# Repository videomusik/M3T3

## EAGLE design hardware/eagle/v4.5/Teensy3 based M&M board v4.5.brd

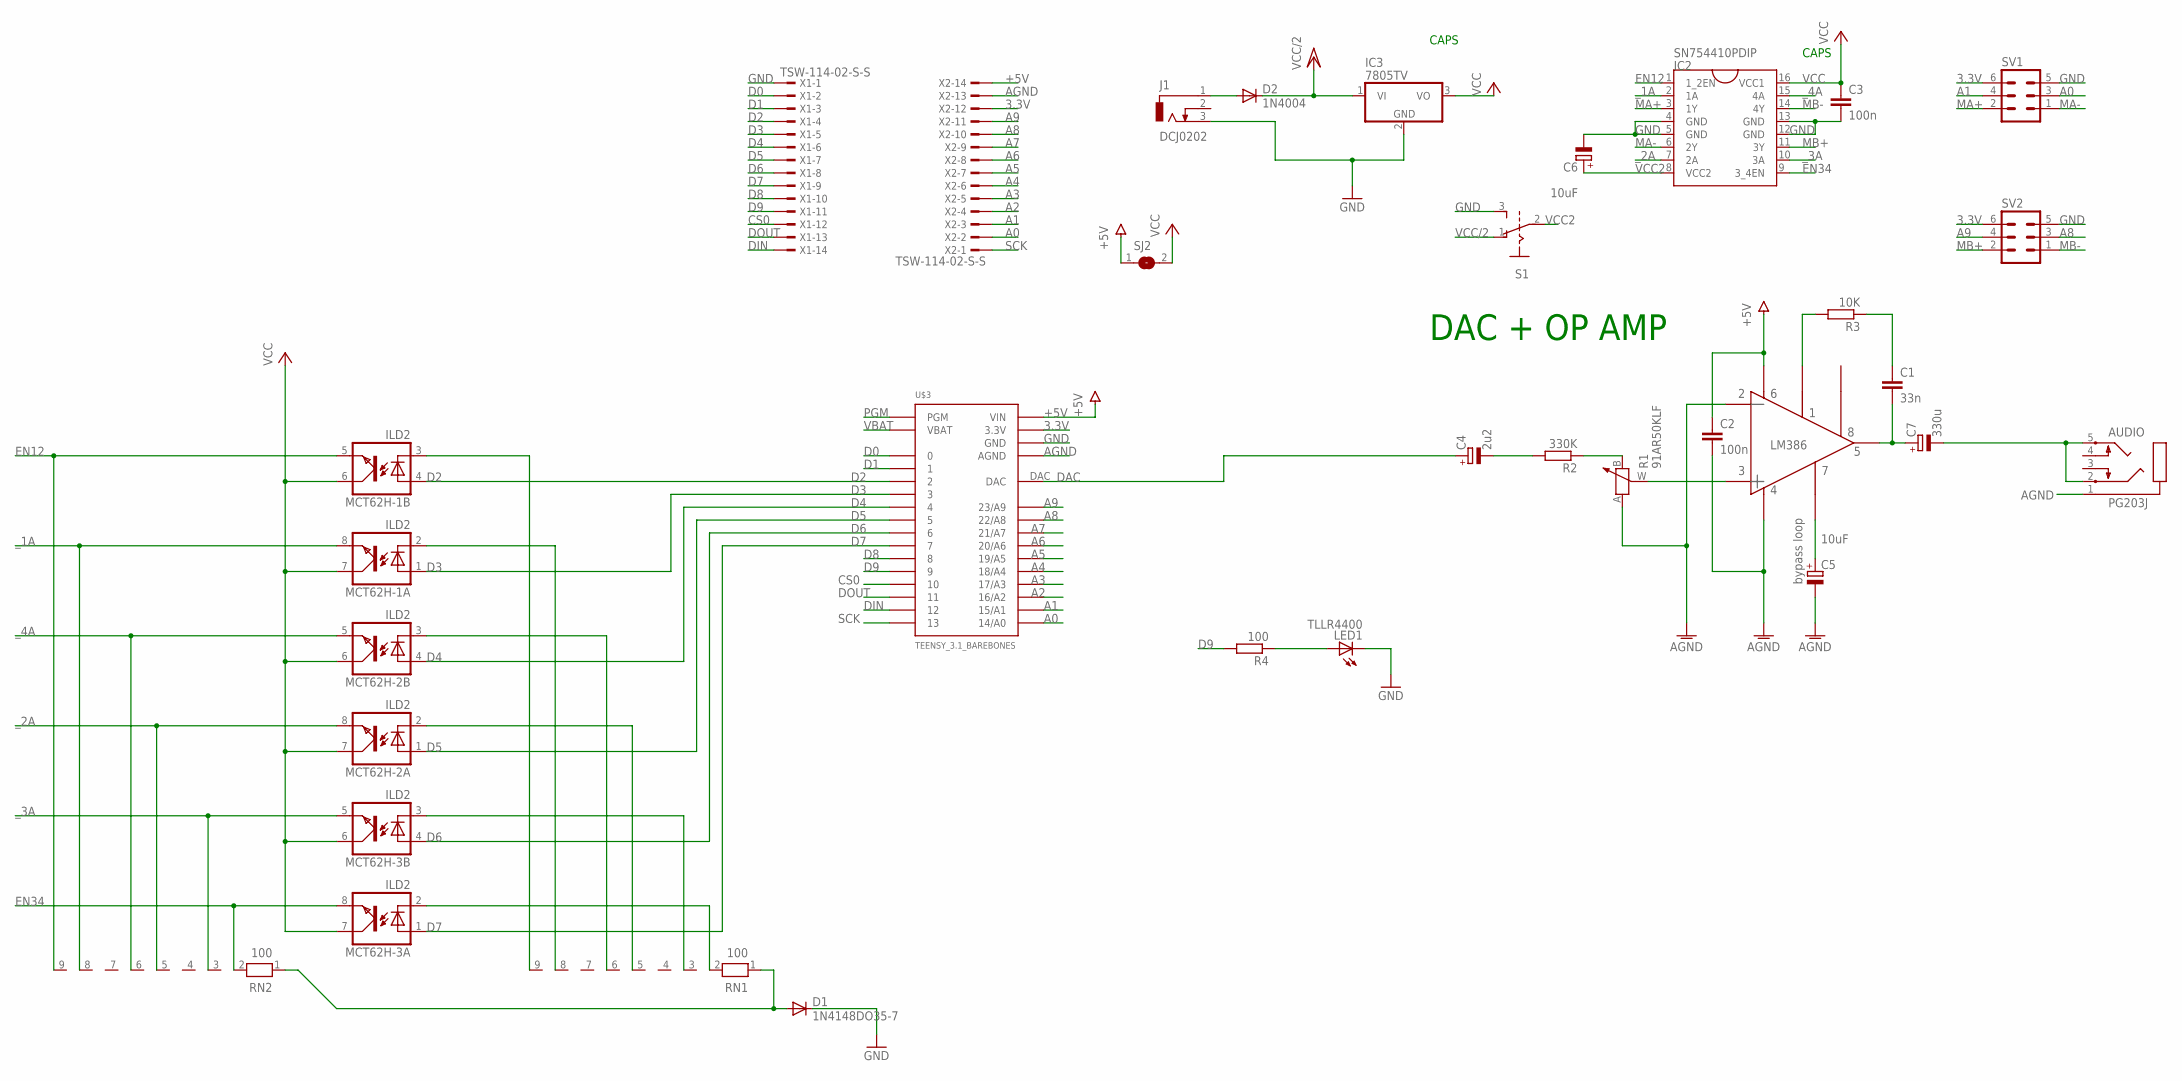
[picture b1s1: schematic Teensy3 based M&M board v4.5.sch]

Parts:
AUDIO: PG203J
C1: 33n; C050-030X075
C2, C3: 100n; C050-030X075
C4: 2u2; E2-5
C5, C6: 10uF; E2-5
C7: 330u; E2,5-7
D1: 1N4148DO35-7; DO35-7
D2: 1N4004; DO41-10
IC2: SN754410PDIP; DIL16
IC3: 7805TV; TO220V
J1: DCJ0202
LED1: TLLR4400; LED3MM
MCT62H-1, MCT62H-2, MCT62H-3: ILD2; DIL08
R1: 91AR50KLF
R2: 330K; 0207/7
R3: 10K; 0207/7
R4: 100; 0207/7
RN1, RN2: 100; RN-9
S1: EG1218; GF-126-0159
SJ2: SJ
SV1, SV2: ML6
U$2: LM386
U$3: TEENSY_3.1_BAREBONES
X1, X2: TSW-114-02-S-S

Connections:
3.3V: SV1.6, SV2.6, U$3.3.3V1 (3.3V), U$3.3.3V2 (3.3V), X2.12
+5V: C2.1, SJ2.1, U$2.6, U$3.VIN, X2.14
A0: SV1.3, U$3.14/A0, X2.2
A1: SV1.4, U$3.15/A1, X2.3
A2: U$3.16/A2, X2.4
A3: U$3.17/A3, X2.5
A4: U$3.18/A4, X2.6
A5: U$3.19/A5, X2.7
A6: U$3.20/A6, X2.8
A7: U$3.21/A7, X2.9
A8: SV2.3, U$3.22/A8, X2.10
A9: SV2.4, U$3.23/A9, X2.11
AGND: AUDIO.1, C2.2, C5.-, R1.A, U$2.2, U$2.4, U$3.AGND, X2.13
AMP_IN: R1.W, U$2.3
CS0: U$3.10, X1.12
D0: U$3.0, X1.2
D1: U$3.1, X1.3
D2: MCT62H-1.4 (A), U$3.2, X1.4
D3: MCT62H-1.1 (A), U$3.3, X1.5
D4: MCT62H-2.4 (A), U$3.4, X1.6
D5: MCT62H-2.1 (A), U$3.5, X1.7
D6: MCT62H-3.4 (A), U$3.6, X1.8
D7: MCT62H-3.1 (A), U$3.7, X1.9
D8: U$3.8, X1.10
D9: R4.2, U$3.9, X1.11
DAC: C4.+, U$3.DAC
DIN: U$3.12, X1.14
DOUT: U$3.11, X1.13
EN12: IC2.1 (1_2EN), MCT62H-1.5 (EMIT), RN2.9
EN34: IC2.9 (3_4EN), MCT62H-3.8 (EMIT), RN2.2
GND: C3.2, C6.-, D1.C, IC2.4 (GND), IC2.5 (GND), IC2.12 (GND), IC2.13 (GND), IC3.2 (GND), J1.3, LED1.K (C), S1.3, SV1.5, SV2.5, U$3.GND1 (GND), U$3.GND2 (GND), X1.1
MA+: IC2.3 (1Y), SV1.2
MA-: IC2.6 (2Y), SV1.1
MB+: IC2.11 (3Y), SV2.2
MB-: IC2.14 (4Y), SV2.1
unnamed: D2.A, J1.1
unnamed: R3.2, U$2.1
unnamed: C4.-, R2.2
unnamed: LED1.A, R4.1
unnamed: R1.B, R2.1
unnamed: D1.A, RN1.1, RN2.1
unnamed: C1.1, R3.1
unnamed: C5.+, U$2.7
unnamed: MCT62H-3.2 (C), RN1.2
unnamed: MCT62H-1.3 (C), RN1.9
unnamed: MCT62H-1.2 (C), RN1.8
unnamed: MCT62H-2.3 (C), RN1.6
unnamed: MCT62H-2.2 (C), RN1.5
unnamed: MCT62H-3.3 (C), RN1.3
unnamed: AUDIO.2, AUDIO.5, C7.-
unnamed: C1.2, C7.+, U$2.5
PGM: U$3.PGM
SCK: U$3.13, X2.1
VBAT: U$3.VBAT
VCC: C3.1, IC2.16 (VCC1), IC3.3 (VO), MCT62H-1.6 (COL), MCT62H-1.7 (COL), MCT62H-2.6 (COL), MCT62H-2.7 (COL), MCT62H-3.6 (COL), MCT62H-3.7 (COL), SJ2.2
VCC2: C6.+, IC2.8 (VCC2), S1.2
VCC/2: D2.C, IC3.1 (VI), S1.1
_1A: IC2.2 (1A), MCT62H-1.8 (EMIT), RN2.8
_2A: IC2.7 (2A), MCT62H-2.8 (EMIT), RN2.5
_3A: IC2.10 (3A), MCT62H-3.5 (EMIT), RN2.3
_4A: IC2.15 (4A), MCT62H-2.5 (EMIT), RN2.6

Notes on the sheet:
DAC + OP AMP
bypass loop
CAPS

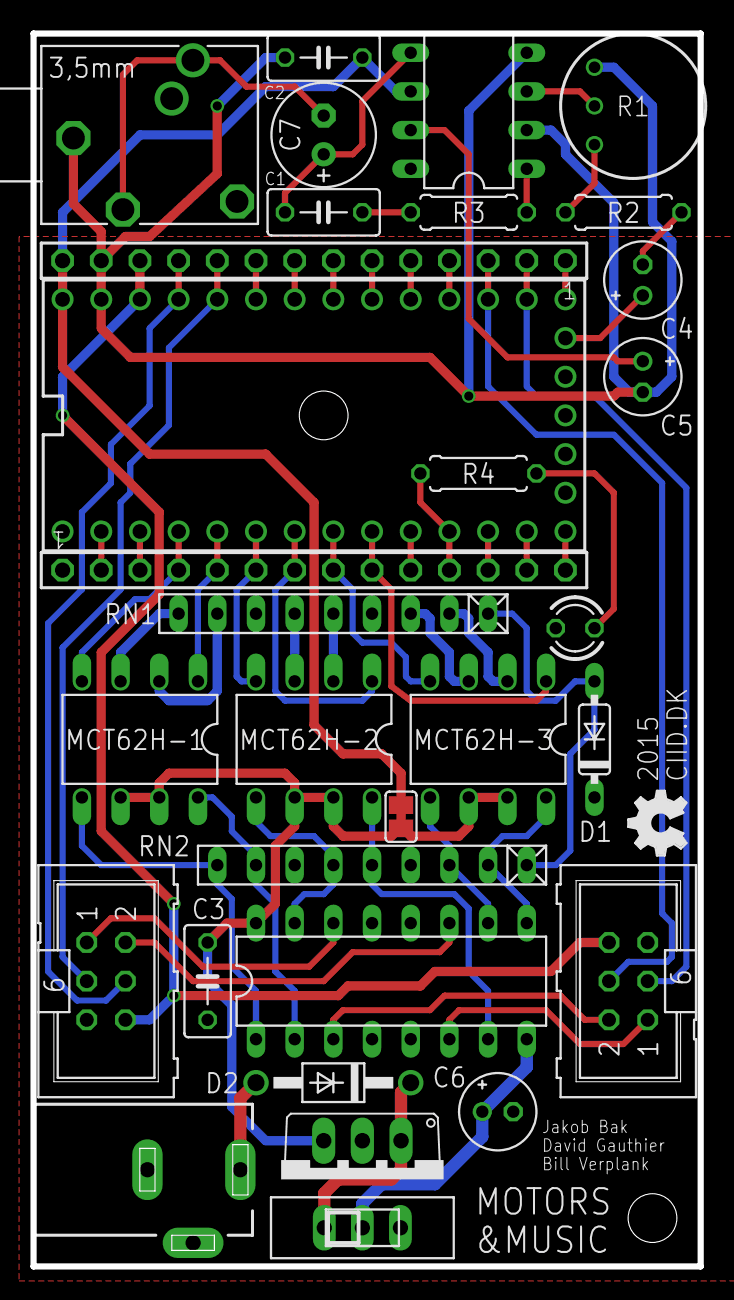
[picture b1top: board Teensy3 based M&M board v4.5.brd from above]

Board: 4 copper layers, 43.8 x 81.0 mm, 32 parts (0 on the bottom side), 59 nets.

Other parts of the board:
U$1: OSHW_FILLX150_NOTEXT

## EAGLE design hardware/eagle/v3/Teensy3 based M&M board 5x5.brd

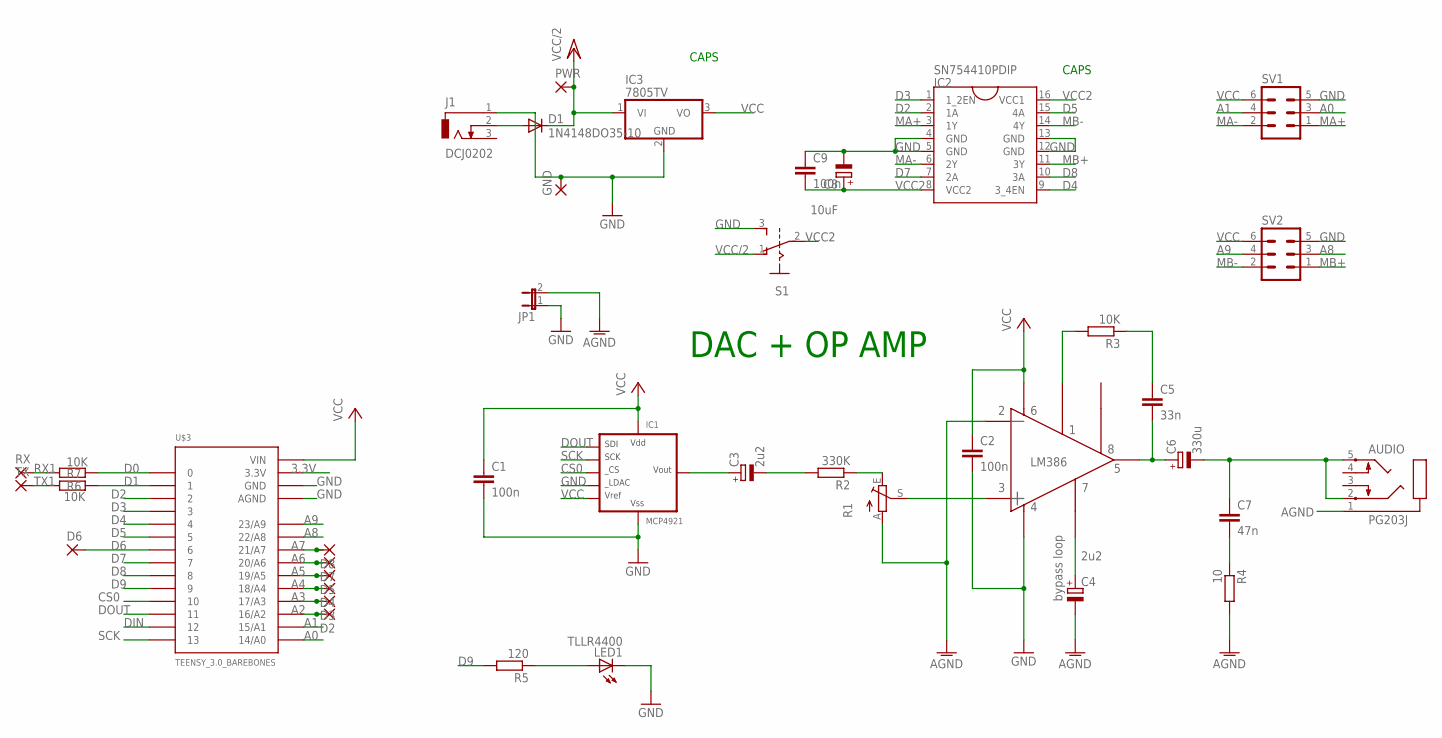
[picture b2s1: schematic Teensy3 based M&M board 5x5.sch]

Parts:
AUDIO: PG203J
C1, C2, C9: 100n; C050-030X075
C3, C4: 2u2; E2-5
C5: 33n; C050-030X075
C6: 330u; E2,5-7
C7: 47n; C050-030X075
C8: 10uF; E2-5
D1: 1N4148DO35-10; DO35-10
D2, D3, D4, D5, D6, D7, D8: 2,15/1,0
GND: 2,15/1,0
IC1: MCP4921; DIL8
IC2: SN754410PDIP; DIL16
IC3: 7805TV; TO220V
J1: DCJ0202
JP1: JP1E; JP1
LED1: TLLR4400; LED3MM
PWR: 2,15/1,0
R1: TRIM_EU-CA9V; CA9V
R2: 330K; 0207/10
R3, R6, R7: 10K; 0207/10
R4: 10; 0207/10
R5: 120; 0207/10
RX: 2,15/1,0
S1: EG1218; GF-126-0159
SV1, SV2: ML6
TX: 2,15/1,0
U$2: LM386
U$3: TEENSY_3.0_BAREBONES

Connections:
3.3V: U$3.3.3V
A0: SV1.3, U$3.14/A0
A1: SV1.4, U$3.15/A1
A2: D2.1, U$3.16/A2
A3: D3.1, U$3.17/A3
A4: D4.1, U$3.18/A4
A5: D5.1, U$3.19/A5
A6: D7.1, U$3.20/A6
A7: D8.1, U$3.21/A7
A8: SV2.3, U$3.22/A8
A9: SV2.4, U$3.23/A9
AGND: AUDIO.1, C4.-, JP1.2, R1.A, R4.2, U$2.2
AMP_IN: R1.S, U$2.3
CS0: IC1.2 (CS), U$3.10
D0: R7.1, U$3.0
D1: R6.1, U$3.1
D2: IC2.2 (1A), U$3.2
D3: IC2.1 (1_2EN), U$3.3
D4: IC2.9 (3_4EN), U$3.4
D5: IC2.15 (4A), U$3.5
D6: D6.1, U$3.6
D7: IC2.7 (2A), U$3.7
D8: IC2.10 (3A), U$3.8
D9: R5.2, U$3.9
DAC_OUT: C3.+, IC1.8 (VOUT)
DIN: U$3.12
DOUT: IC1.4 (SDI), U$3.11
GND: C1.2, C2.2, C8.-, C9.1, GND.1, IC1.5 (LDAC), IC1.7 (VSS), IC2.4 (GND), IC2.5 (GND), IC2.12 (GND), IC2.13 (GND), IC3.2 (GND), J1.1, JP1.1, LED1.K (C), S1.3, SV1.5, SV2.5, U$2.4, U$3.AGND, U$3.GND
MA+: IC2.3 (1Y), SV1.1
MA-: IC2.6 (2Y), SV1.2
MB+: IC2.11 (3Y), SV2.1
MB-: IC2.14 (4Y), SV2.2
unnamed: D1.A, J1.2
unnamed: R3.2, U$2.1
unnamed: C3.-, R2.2
unnamed: R1.E, R2.1
unnamed: LED1.A, R5.1
unnamed: C5.1, R3.1
unnamed: C4.+, U$2.7
unnamed: C7.2, R4.1
unnamed: AUDIO.2, AUDIO.5, C6.-, C7.1
unnamed: C5.2, C6.+, U$2.5
RX1: R7.2, RX.1
SCK: IC1.3 (SCK), U$3.13
TX1: R6.2, TX.1
VCC: C1.1, C2.1, IC1.1 (VDD), IC1.6 (VREF), IC3.3 (VO), SV1.6, SV2.6, U$2.6, U$3.VIN
VCC2: C8.+, C9.2, IC2.8 (VCC2), IC2.16 (VCC1), S1.2
VCC/2: D1.C, IC3.1 (VI), PWR.1, S1.1

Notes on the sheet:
DAC + OP AMP
bypass loop
CAPS

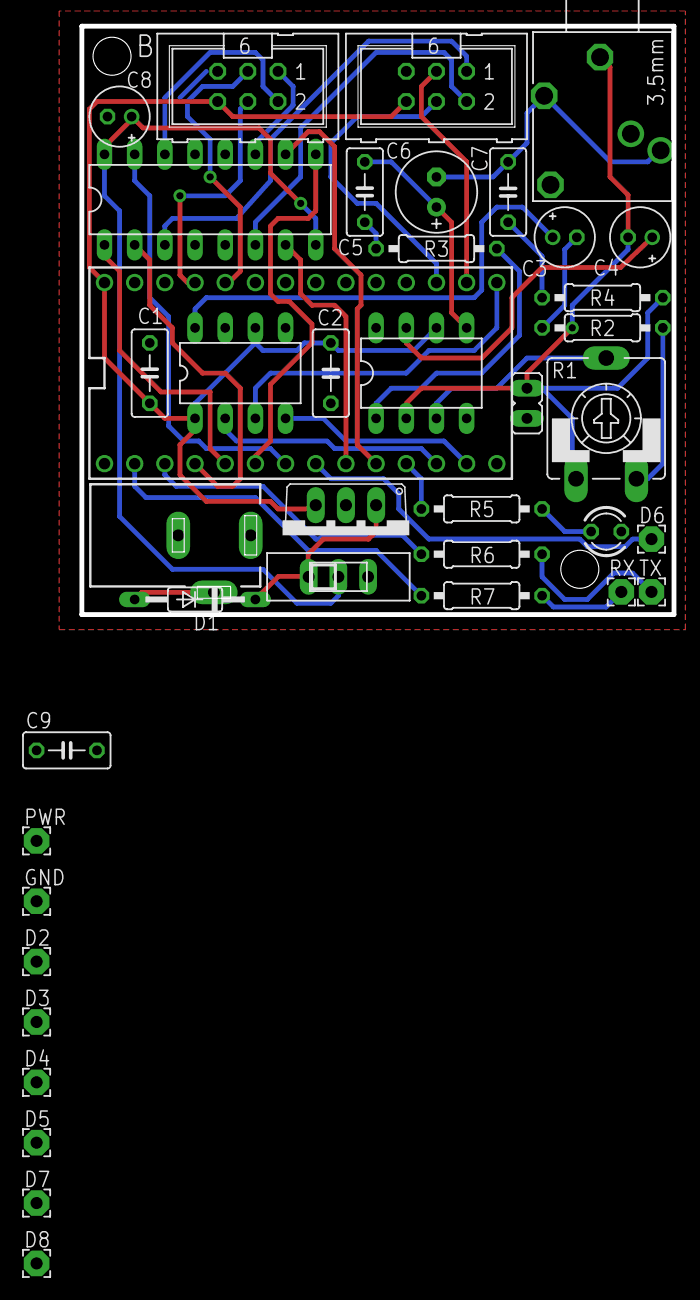
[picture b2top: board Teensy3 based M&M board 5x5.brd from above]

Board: 4 copper layers, 49.8 x 49.5 mm, 40 parts (0 on the bottom side), 46 nets.

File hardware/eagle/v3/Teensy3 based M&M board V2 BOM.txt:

Partlist exported from /Users/videomusik/Dropbox/Physical Computing/Eagle/Teensy3 based M&M board/Teensy3 based M&M board V2.sch at 9/12/13 2:21 PM

Part  Value                Device               Package              Description                                                  
AUDIO PG203J               PG203J               PG203J               MIC/HEADPHONE JACK                                           
C1    100n                 C-EU050-030X075      C050-030X075         CAPACITOR, European symbol                                   
C2    100n                 C-EU050-030X075      C050-030X075         CAPACITOR, European symbol                                   
C3    2u2                  CPOL-EUE2-5          E2-5                 POLARIZED CAPACITOR, European symbol                         
C4    2u2                  CPOL-EUE2-5          E2-5                 POLARIZED CAPACITOR, European symbol                         
C5    33n                  C-EU050-030X075      C050-030X075         CAPACITOR, European symbol                                   
C6    330u                 CPOL-EUE2.5-7        E2,5-7               POLARIZED CAPACITOR, European symbol                         
C7    47n                  C-EU050-030X075      C050-030X075         CAPACITOR, European symbol                                   
C8    10uF                 CPOL-EUE2-5          E2-5                 POLARIZED CAPACITOR, European symbol                         
C9    100n                 C-EU050-030X075      C050-030X075         CAPACITOR, European symbol                                   
D1    1N4148DO35-10        1N4148DO35-10        DO35-10              DIODE                                                        
D6                         2,15/1,0             2,15/1,0             THROUGH-HOLE PAD                                             
IC1   MCP4921              MCP4921P             DIL8                 MCP4921: 12-bit DAC                                          
IC2   SN754410PDIP         SN754410PDIP         DIL16                                                                             
IC3   7805TV               7805TV               TO220V               Positive VOLTAGE REGULATOR                                   
J1    DCJ0202              DCJ0202              DCJ0202              DC POWER JACK                                                
LED1  TLLR4400             TLLR4400             LED3MM               Low Current (2mA) LED 3 mm Tinted Diffused Package color RED 
R1                         TRIM_EU-CA9V         CA9V                 POTENTIOMETER                                                
R2    330K                 R-EU_0207/10         0207/10              RESISTOR, European symbol                                    
R3    10K                  R-EU_0207/10         0207/10              RESISTOR, European symbol                                    
R4    10                   R-EU_0207/10         0207/10              RESISTOR, European symbol                                    
R5    120                  R-EU_0207/10         0207/10              RESISTOR, European symbol                                    
R6    10K                  R-EU_0207/10         0207/10              RESISTOR, European symbol                                    
R7    10K                  R-EU_0207/10         0207/10              RESISTOR, European symbol                                    
RX                         2,15/1,0             2,15/1,0             THROUGH-HOLE PAD                                             
S1                         EG1218               GF-126-0159                                                                       
SJ1                        SJ                   SJ                   SMD solder JUMPER                                            
SV1                        ML6                  ML6                  HARTING                                                      
SV2                        ML6                  ML6                  HARTING                                                      
TX                         2,15/1,0             2,15/1,0             THROUGH-HOLE PAD                                             
U$2   LM386                LM386OA              LM386                                                                             
U$3   TEENSY_3.0_BAREBONES TEENSY_3.0_BAREBONES TEENSY_3.0_BAREBONES                                                              
X2    TSW-114-02-S-S       TSW-114-02-S-S       TSW-114-02-S-S       THROUGH-HOLE .025" SQ POST HEADER

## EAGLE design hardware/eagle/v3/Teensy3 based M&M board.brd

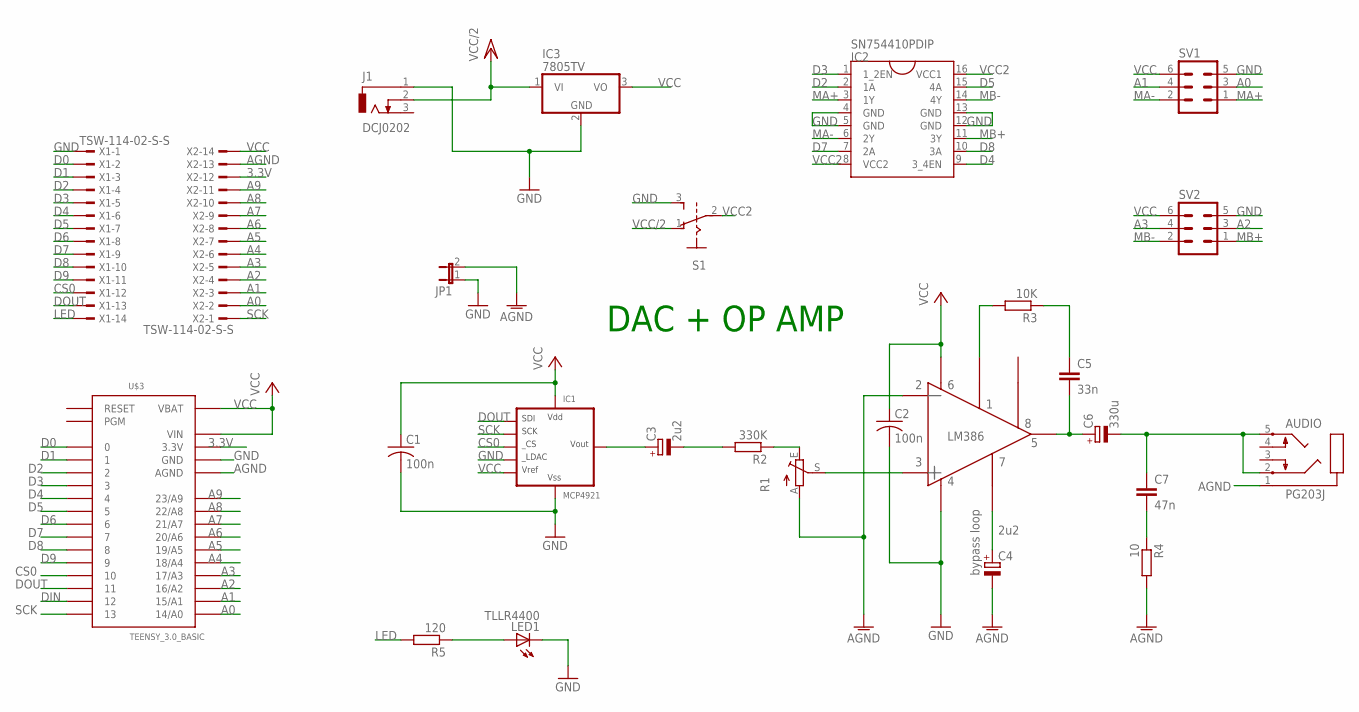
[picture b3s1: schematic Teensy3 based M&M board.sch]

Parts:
AUDIO: PG203J
C1, C2: 100n; C050-035X075
C3, C4: 2u2; E2-5
C5: 33n; C050-024X044
C6: 330u; E2,5-7
C7: 47n; C050-024X044
IC1: MCP4921; DIL8
IC2: SN754410PDIP; DIL16
IC3: 7805TV; TO220V
J1: DCJ0202
JP1: JP1E; JP1
LED1: TLLR4400; LED3MM
R1: TRIM_EU-CA9V; CA9V
R2: 330K; 0207/10
R3: 10K; 0207/10
R4: 10; 0207/10
R5: 120; 0207/10
S1: EG1218; GF-126-0159
SV1, SV2: ML6
U$2: LM386
U$3: TEENSY_3.0_BASIC
X1, X2: TSW-114-02-S-S

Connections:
3.3V: U$3.3.3V, U$3.3.3V1 (3.3V), X2.12
A0: SV1.3, U$3.14/A0, X2.2
A1: SV1.4, U$3.15/A1, X2.3
A2: SV2.3, U$3.16/A2, X2.4
A3: SV2.4, U$3.17/A3, X2.5
A4: U$3.18/A4, X2.6
A5: U$3.19/A5, X2.7
A6: U$3.20/A6, X2.8
A7: U$3.21/A7, X2.9
A8: U$3.22/A8, X2.10
A9: U$3.23/A9, X2.11
AGND: AUDIO.1, C4.-, JP1.2, R1.A, R4.2, U$2.2, U$3.AGND, X2.13
CS0: IC1.2 (CS), U$3.10, X1.12
D0: U$3.0, X1.2
D1: U$3.1, X1.3
D2: IC2.2 (1A), U$3.2, X1.4
D3: IC2.1 (1_2EN), U$3.3, X1.5
D4: IC2.9 (3_4EN), U$3.4, X1.6
D5: IC2.15 (4A), U$3.5, X1.7
D6: U$3.6, X1.8
D7: IC2.7 (2A), U$3.7, X1.9
D8: IC2.10 (3A), U$3.8, X1.10
D9: U$3.9, X1.11
DIN: U$3.12
DOUT: IC1.4 (SDI), U$3.11, X1.13
GND: C1.2, C2.2, IC1.5 (LDAC), IC1.7 (VSS), IC2.4 (GND), IC2.5 (GND), IC2.12 (GND), IC2.13 (GND), IC3.2 (GND), J1.1, JP1.1, LED1.K (C), S1.3, SV1.5, SV2.5, U$2.4, U$3.GND, U$3.GND1 (GND), X1.1
LED: R5.2, X1.14
MA+: IC2.3 (1Y), SV1.1
MA-: IC2.6 (2Y), SV1.2
MB+: IC2.11 (3Y), SV2.1
MB-: IC2.14 (4Y), SV2.2
unnamed: C3.+, IC1.8 (VOUT)
unnamed: R3.2, U$2.1
unnamed: C3.-, R2.2
unnamed: R1.E, R2.1
unnamed: LED1.A, R5.1
unnamed: C5.1, R3.1
unnamed: C4.+, U$2.7
unnamed: C7.2, R4.1
unnamed: R1.S, U$2.3
unnamed: AUDIO.2, AUDIO.5, C6.-, C7.1
unnamed: C5.2, C6.+, U$2.5
SCK: IC1.3 (SCK), U$3.13, X2.1
VCC: C1.1, C2.1, IC1.1 (VDD), IC1.6 (VREF), IC3.3 (VO), SV1.6, SV2.6, U$2.6, U$3.VBAT, U$3.VIN, X2.14
VCC2: IC2.8 (VCC2), IC2.16 (VCC1), S1.2
VCC/2: IC3.1 (VI), J1.2, S1.1

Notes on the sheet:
DAC + OP AMP
bypass loop

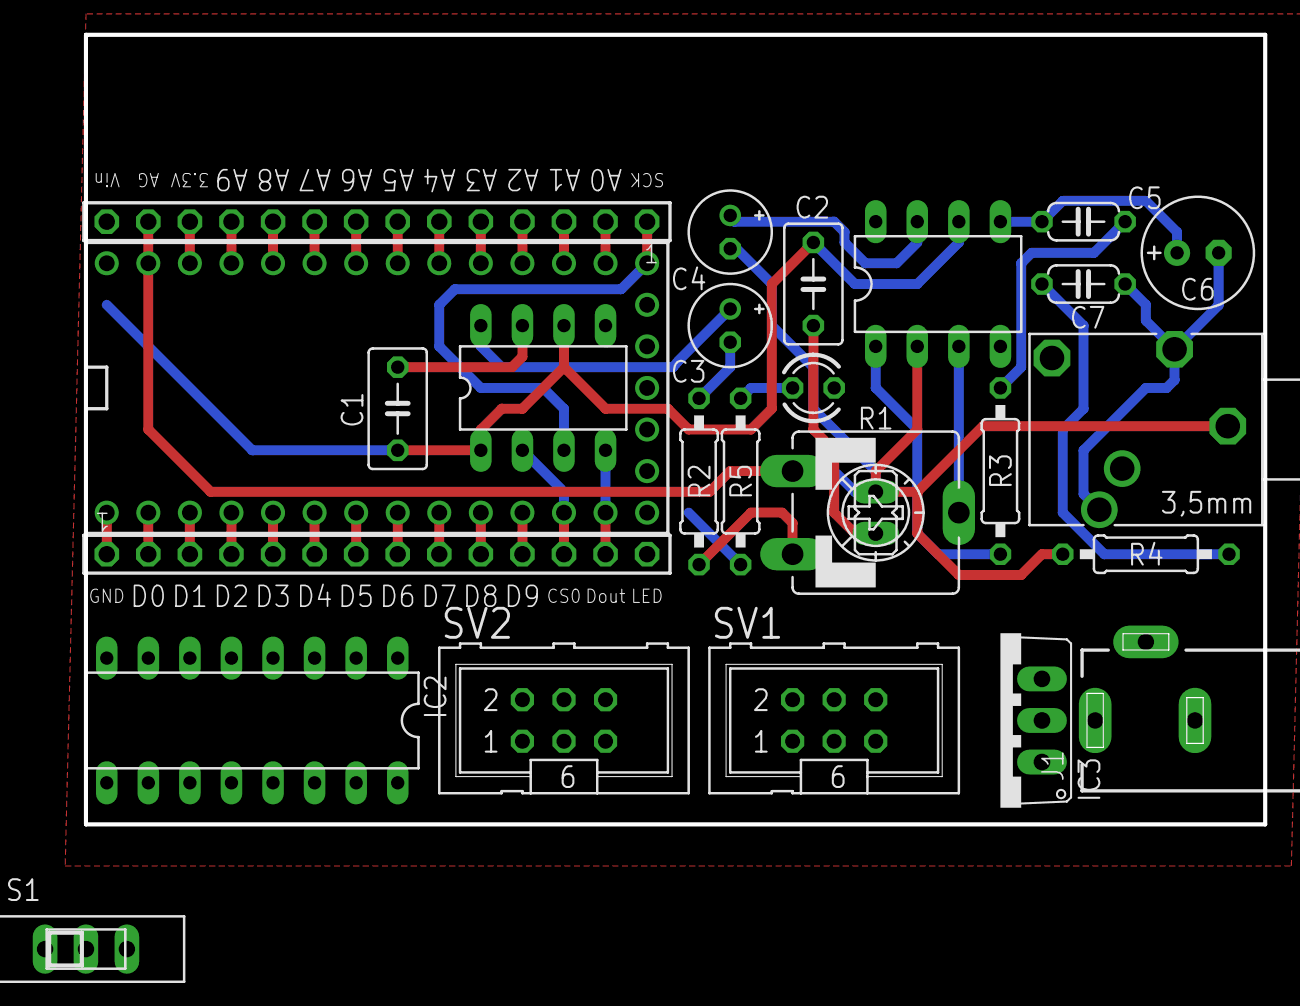
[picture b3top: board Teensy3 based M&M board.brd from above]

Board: 4 copper layers, 72.1 x 48.2 mm, 26 parts (0 on the bottom side), 45 nets.

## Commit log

2013-09-19 Updating folder structure to new Project
2013-09-22 lots of changes
2013-11-29 Added MotionT3 library and Monotron Filter support
2013-12-18 changes to filter control
2014-05-20 Added updated synth engine and new eagle files
2014-05-25 updated Motor example "_1_centering"
2014-05-30 updated examples to work with current library
2014-05-30 Added Max Standalone Application Dashboard
2014-06-05 fixed usbMidi dependency when not using MIDI
2014-06-10 added filter and removed MAX/MSP dashboard
2014-06-10 fixed Motion offset
2014-06-10 Oscilloscope and ForceProfile fixes (work-in-pro)
2014-06-10 Merge branch 'master' of https://github.com/videomusik/M3T3
    Conflicts:
    software/lib/M3T3/MotionT3.h
2014-06-10 removed github changes
2014-06-11 Added Sequencer
2014-06-17 disabled MIDI calls to enableEnvelope
2015-04-19 updated sound and motor functions to all work on 12bit internally
2015-04-20 new oscillator headers
2015-04-21 enable T3DAC
2015-04-21 no inline in cpp
2015-04-22 Updated M3T3 library with new sound code
2015-04-23 window height change
